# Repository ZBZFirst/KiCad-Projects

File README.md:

# ESP32 Controller

---

## Reference Images

### PCB Layout

### Attachment

### Finished Build

---

Custom ESP32 BLE HID controller + matching PCB design.

This project combines:

- ESP32 firmware (BLE composite keyboard + mouse)
- KiCad PCB layout for a dedicated 7-button controller
- Multi-mode input system for productivity + automation

Designed as a personal hardware controller that behaves like a wireless keyboard/mouse macro pad.

---

## Features

- BLE composite HID device (keyboard + mouse)
- 7 physical buttons
- Mode switching system
- Auto-click / auto-key spam mode
- Windows quick-launch macros
- Non-blocking firmware architecture
- Visual LED status patterns
- Custom PCB layout (KiCad)

---

## Hardware

### Board

ESP32-based custom PCB with:

- 7 tactile switches
- Onboard LED status indicator
- ESP32 dev module header
- Dedicated GPIO routing per button

KiCad layout included in repository.

File:

```
hardware/Controller.kicad_pcb
```

This board is designed specifically to run the included firmware.

---

## Firmware Behavior

The controller has **3 operating groups**.

Button 6 cycles groups.  
Button 7 forces disconnect (reboot).

---

### Group 1 — Default Productivity

| Button | Action |
|--------|--------|
| B1 | Ctrl + C |
| B2 | Ctrl + V |
| B3 | Ctrl + X |
| B4 | Ctrl + Z |
| B5 | 8-second mouse movement run |

LED: solid ON when connected

---

### Group 2 — Work Launch Macros

| Button | Action |
|--------|--------|
| B1 | Windows search → cmd → ssh CB37 |
| B2 | Launch Edge |
| B3 | Launch Super |
| B4 | Launch Arduino |
| B5 | Launch Bluetooth |

LED: 2 blink pattern

---

### Group 3 — Auto Mode

Toggle behaviors:

| Button | Mode |
|--------|------|
| B1 | Auto left click |
| B2 | Auto right click |
| B3 | Auto middle click |
| B4 | Spam key “E” |
| B5 | Spam key “F” |

Press the same button again to stop.

LED: 3 blink pattern

---

## LED Status

- Off → not connected
- Solid → group 1
- 2 blinks → group 2
- 3 blinks → group 3

Blink sequence repeats every 2 seconds.

---

## Installation

### Requirements

- Arduino IDE
- ESP32 board package
- NimBLE / BLE HID libraries

Open:

```
firmware/PaulsESP32.ino
```

Compile and upload to the board.

---

## Usage

1. Power the controller
2. Pair over Bluetooth
3. Use button 6 to select mode
4. Use buttons 1–5 for actions

Designed primarily for Windows but functions as a generic BLE HID device.

---

## Project Structure

```
firmware/
  PaulsESP32.ino

hardware/
  Controller.kicad_pcb
  schematics/
```

---

## Credits

PCB + firmware design: Paul Casillas  
Artwork: Bree Pierce

Personal project.

---

## License

MIT — free to modify and build.

file is in

AutoClicker/AutoClickerbyController.ino

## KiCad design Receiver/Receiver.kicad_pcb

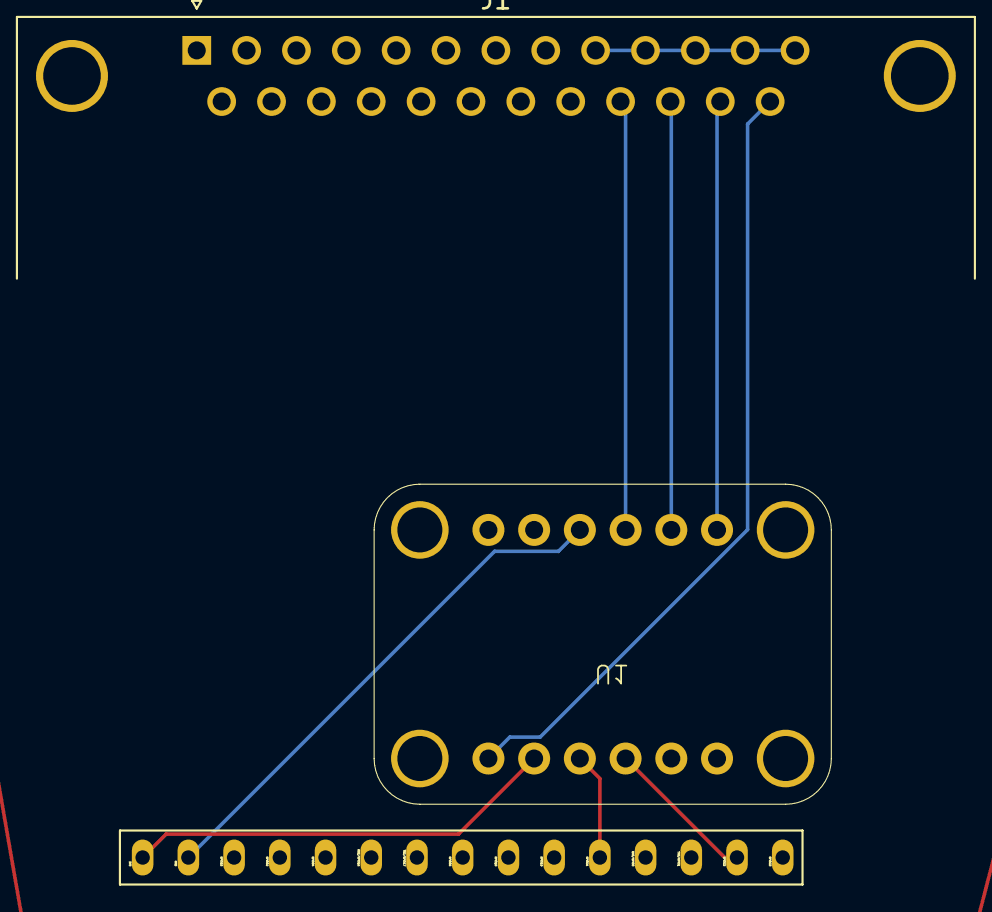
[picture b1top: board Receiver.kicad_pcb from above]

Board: 2 copper layers, 3 parts (1 on the bottom side), 9 nets.

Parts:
ESP32 Right Side1: ESP32-DEVKITV1-Paul-Half2
J1: AveaLogic; DSUB-25_Pins_Horizontal_P2.77x2.84mm_EdgePinOffset9.90mm_Ho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
U1: ADS1115IDGS; ADS1115FootPrint

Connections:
GND: J1.9 (GND), J1.10 (GND), J1.11 (GND), J1.12 (GND), J1.13 (GND)
unnamed: ESP32 Right Side1.54 (3V), U1.8 (VDD)
unnamed: ESP32 Right Side1.53 (GND), U1.3 (GND)
unnamed: ESP32 Right Side1.21 (GPIO21/SDA/SDI), U1.9 (SDA)
unnamed: ESP32 Right Side1.22 (GPIO22/SCL/SCK), U1.10 (SCL)
unnamed: J1.23 (FLOW), U1.5 (AIN1)
unnamed: J1.25 (PHASE), U1.7 (AIN3)
unnamed: J1.22 (PRESSURE), U1.4 (AIN0)
unnamed: J1.24 (VOLUME), U1.6 (AIN2)

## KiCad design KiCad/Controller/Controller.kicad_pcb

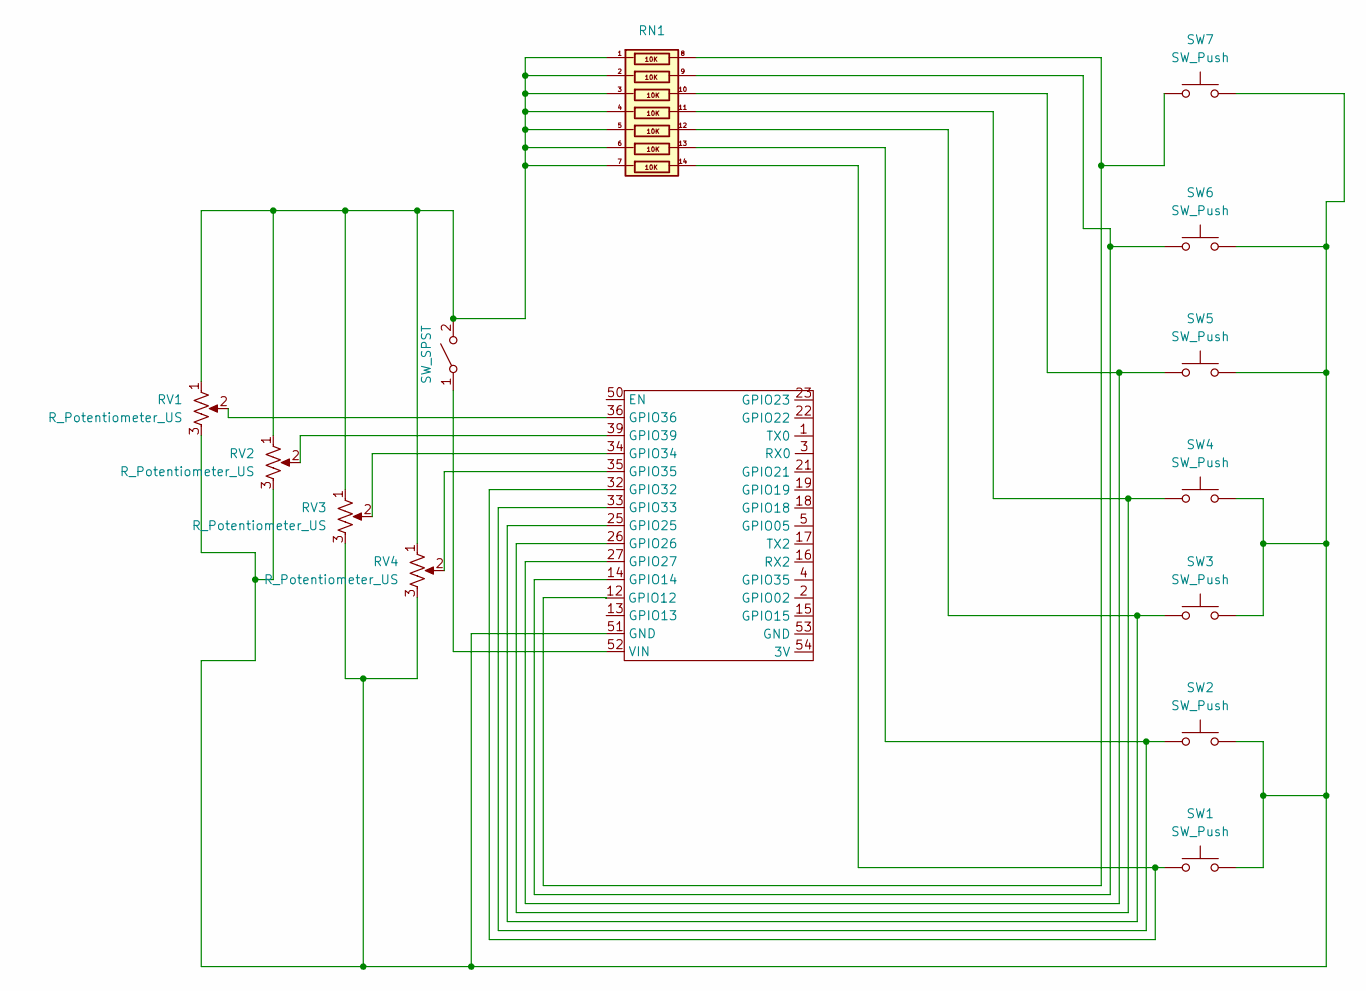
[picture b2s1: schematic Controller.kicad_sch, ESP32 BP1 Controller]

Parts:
RN1: 10K Array
RV1, RV2, RV3, RV4: R_Potentiometer_US; Potentiometer_Alps_RK09Y11_Single_Horizontal
SW1, SW2, SW3, SW4, SW5, SW6, SW7: SW_Push; SW_PUSH_6mm_H5mm
SW9: SW_SPST; SW_DIP_SPSTx01_Slide_9.78x4.72mm_W7.62mm_P2.54mm
U1: ESP32-DEVKITV1-Paul-Half

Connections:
unnamed: RV1.3, RV2.3, RV3.3, RV4.3, SW1.2, SW2.2, SW3.2, SW4.2, SW5.2, SW6.2, SW7.2, U1.51 (GND)
unnamed: RV4.2, U1.35 (GPIO35)
unnamed: SW9.1 (A), U1.52 (VIN)
unnamed: RN1.1 (R1), RN1.2 (R2), RN1.3 (R3), RN1.4 (R4), RN1.5 (R5), RN1.6 (R6), RN1.7 (R7), RV1.1, RV2.1, RV3.1, RV4.1, SW9.2 (B)
unnamed: RN1.8 (R1), SW7.1, U1.12 (GPIO12)
unnamed: RN1.9 (R2), SW6.1, U1.14 (GPIO14)
unnamed: RN1.12 (R5), SW3.1, U1.25 (GPIO25)
unnamed: RN1.11 (R4), SW4.1, U1.26 (GPIO26)
unnamed: RN1.10 (R3), SW5.1, U1.27 (GPIO27)
unnamed: RN1.14 (R7), SW1.1, U1.32 (GPIO32)
unnamed: RN1.13 (R6), SW2.1, U1.33 (GPIO33)
unnamed: RV3.2, U1.34 (GPIO34)
unnamed: RV1.2, U1.36 (GPIO36)
unnamed: RV2.2, U1.39 (GPIO39)

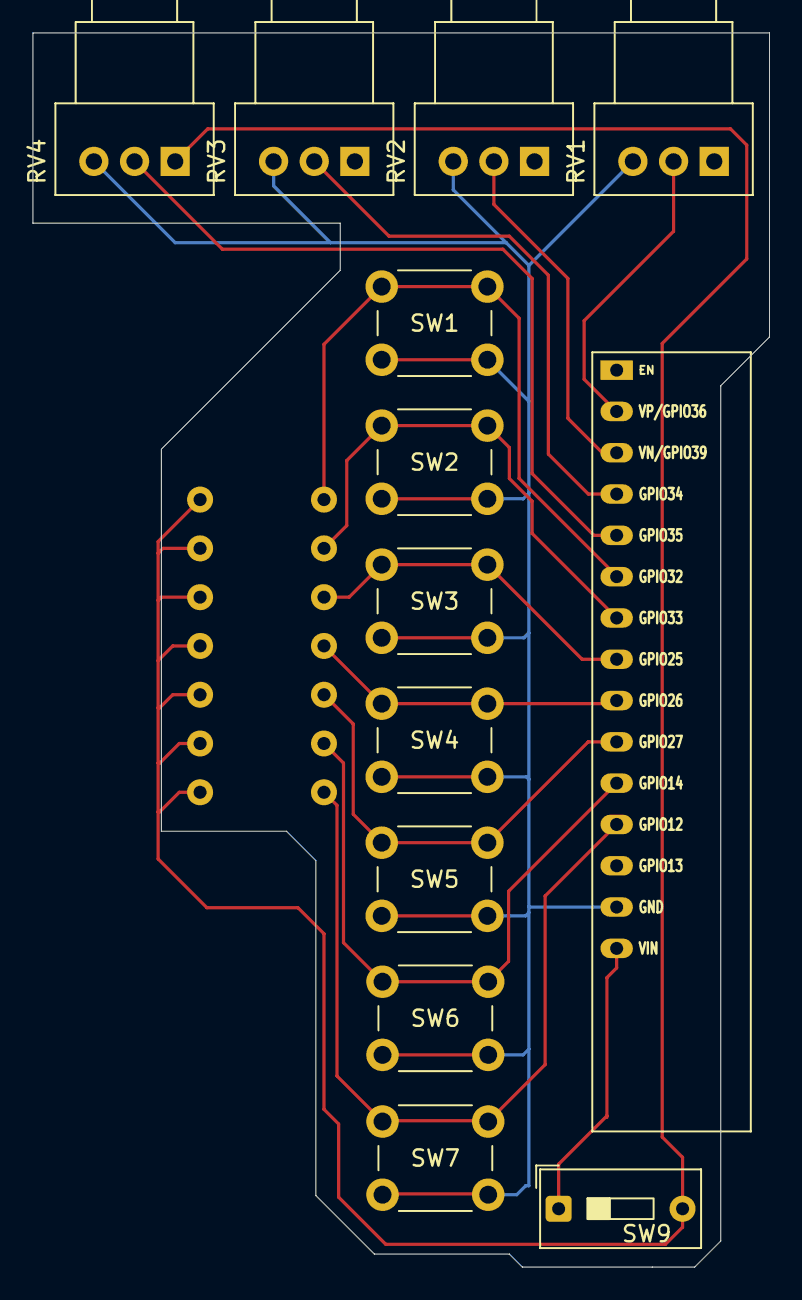
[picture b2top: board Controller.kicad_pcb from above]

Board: 2 copper layers, 45.3 x 75.9 mm, 14 parts (1 on the bottom side), 14 nets.

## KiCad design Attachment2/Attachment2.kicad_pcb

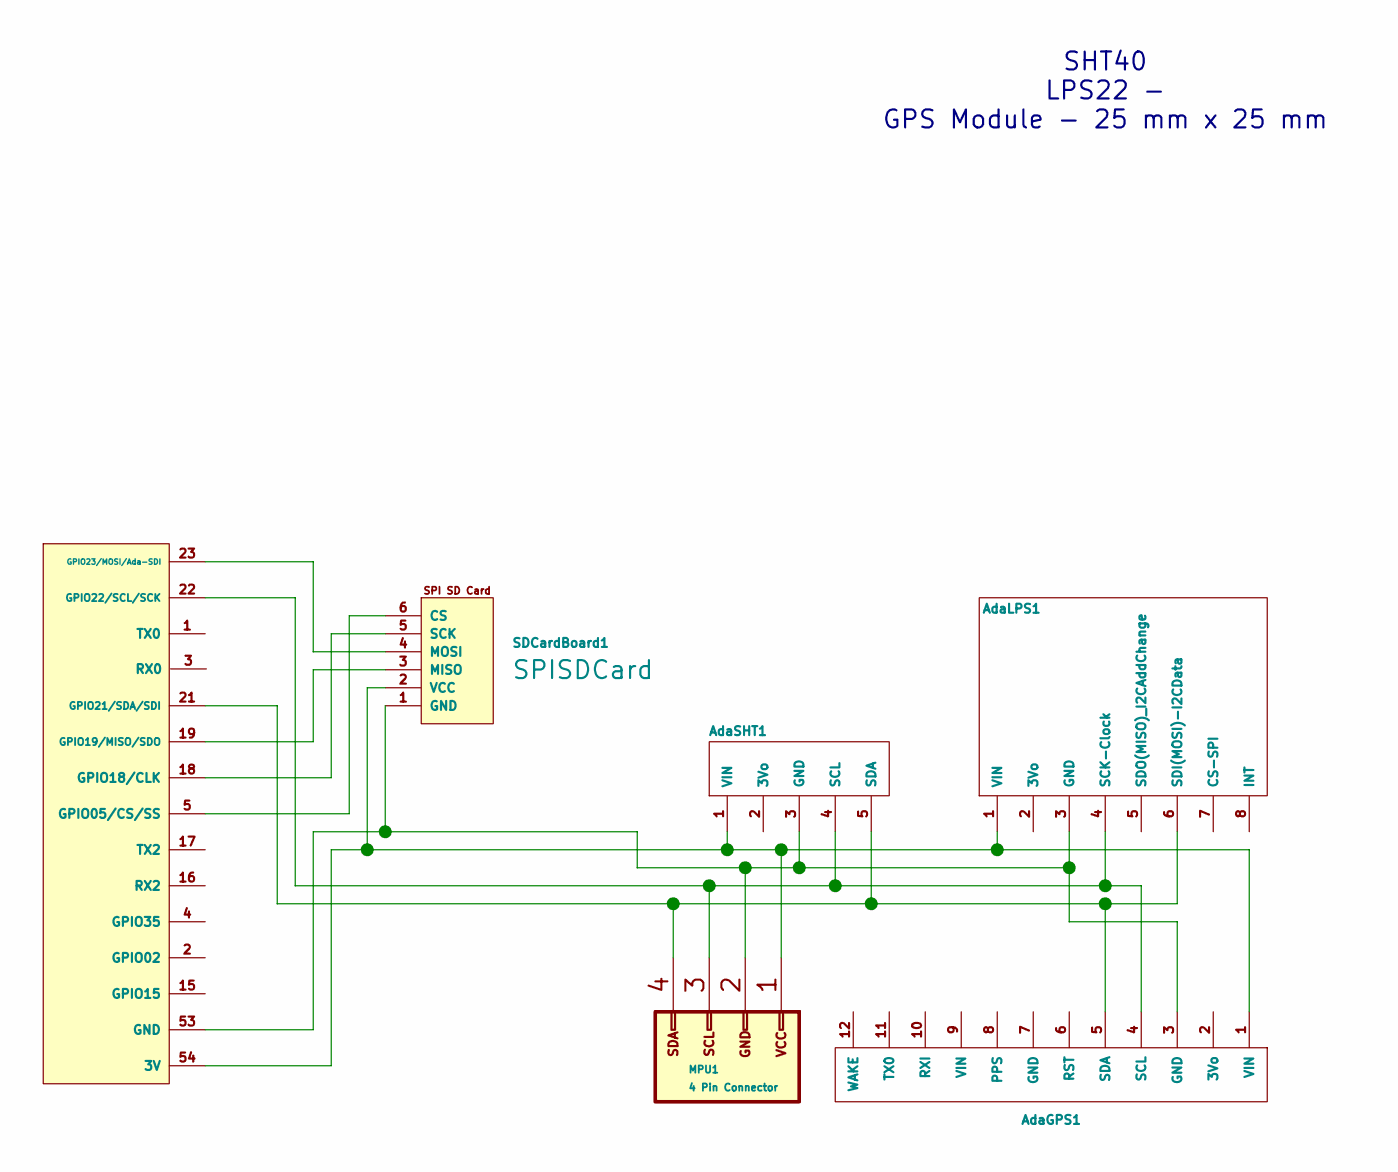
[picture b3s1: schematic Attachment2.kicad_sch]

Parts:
AdaGPS1: Adafruit GPS PA1010D
AdaLPS1: LPS22
AdaSHT1: SHTBoard
ESP32RightSide1: ESP 32 RS; ESP32-DEVKITV1-Paul-Half2
MPU1: 4 Pin Connector; MPU6050HiLetGO
SDCardBoard1: SPISDCard; PinHeader_1x06_P2.54mm_Vertical

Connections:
unnamed: AdaGPS1.4 (SCL), AdaLPS1.4 (SCK-Clock), AdaSHT1.4 (SCL), ESP32RightSide1.22 (GPIO22/SCL/SCK), MPU1.3 (SCL)
unnamed: AdaGPS1.5 (SDA), AdaLPS1.6 (SDI(MOSI)-I2CData), AdaSHT1.5 (SDA), ESP32RightSide1.21 (GPIO21/SDA/SDI), MPU1.4 (SDA)
unnamed: AdaGPS1.3 (GND), AdaLPS1.3 (GND), AdaSHT1.3 (GND), ESP32RightSide1.53 (GND), MPU1.2 (GND), SDCardBoard1.1 (GND)
unnamed: AdaGPS1.1 (VIN), AdaLPS1.1 (VIN), AdaSHT1.1 (VIN), ESP32RightSide1.54 (3V), MPU1.1 (VCC), SDCardBoard1.2 (VCC)
unnamed: ESP32RightSide1.5 (GPIO05/CS/SS), SDCardBoard1.6 (CS)
unnamed: ESP32RightSide1.18 (GPIO18/CLK), SDCardBoard1.5 (SCK)
unnamed: ESP32RightSide1.19 (GPIO19/MISO/SDO), SDCardBoard1.3 (MISO)
unnamed: ESP32RightSide1.23 (GPIO23/MOSI/Ada-SDI), SDCardBoard1.4 (MOSI)

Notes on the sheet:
SHT40 LPS22 - GPS Module - 25 mm x 25 mm

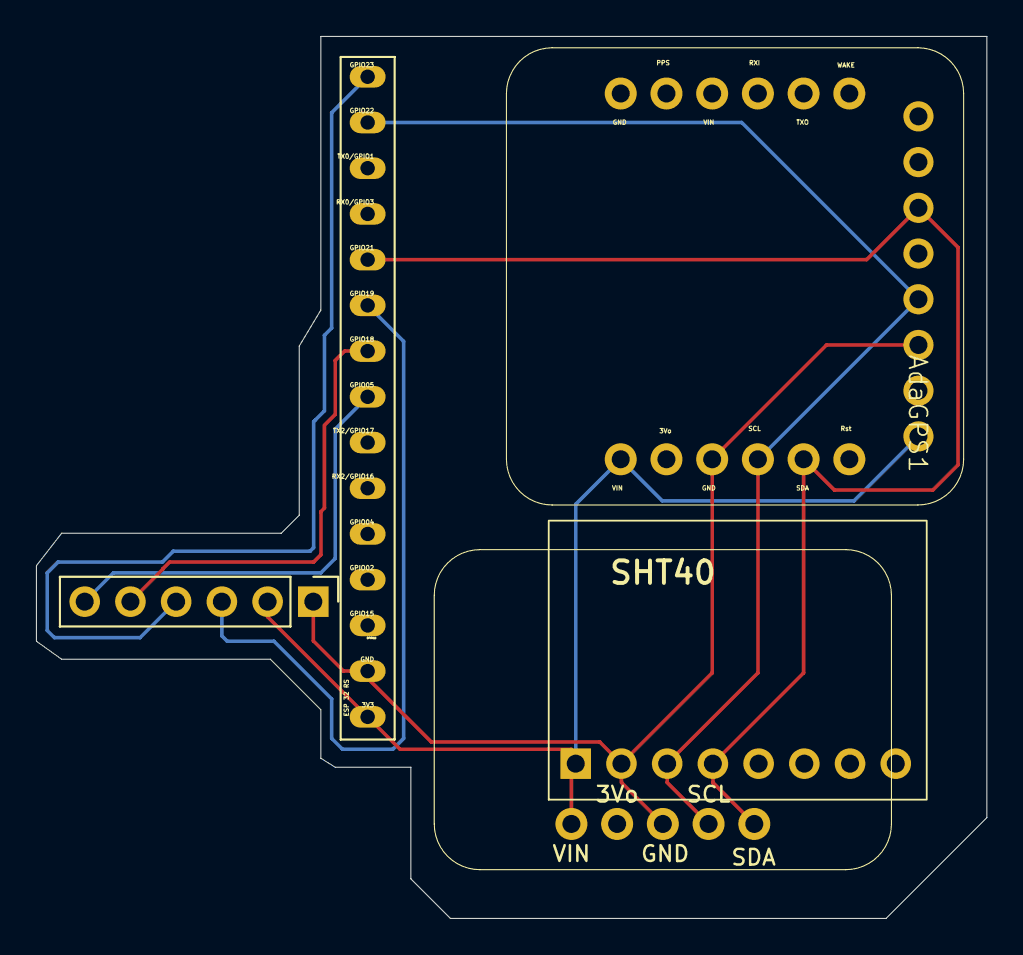
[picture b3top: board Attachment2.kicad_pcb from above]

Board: 2 copper layers, 52.8 x 49.0 mm, 6 parts (0 on the bottom side), 8 nets.

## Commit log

2025-09-10 Backup local KiCad projects into repo
2025-09-10 Backup all KiCad projects into repo/KiCad folder
2025-09-15 9-15-25 test upload from puter
2025-11-20 Implement BLE mouse with MPU6050 and touch sensors
    This code implements a BLE mouse using an ESP32 and MPU6050 sensor. It includes touch sensor handling for mouse buttons and toggles between relative and absolute mouse modes.
2026-02-16 Add reference images to README
    Added reference images for PCB layout, attachment, and finished build.
2026-02-16 Revise project title and update image formatting
    Updated README to change project title and image syntax.
